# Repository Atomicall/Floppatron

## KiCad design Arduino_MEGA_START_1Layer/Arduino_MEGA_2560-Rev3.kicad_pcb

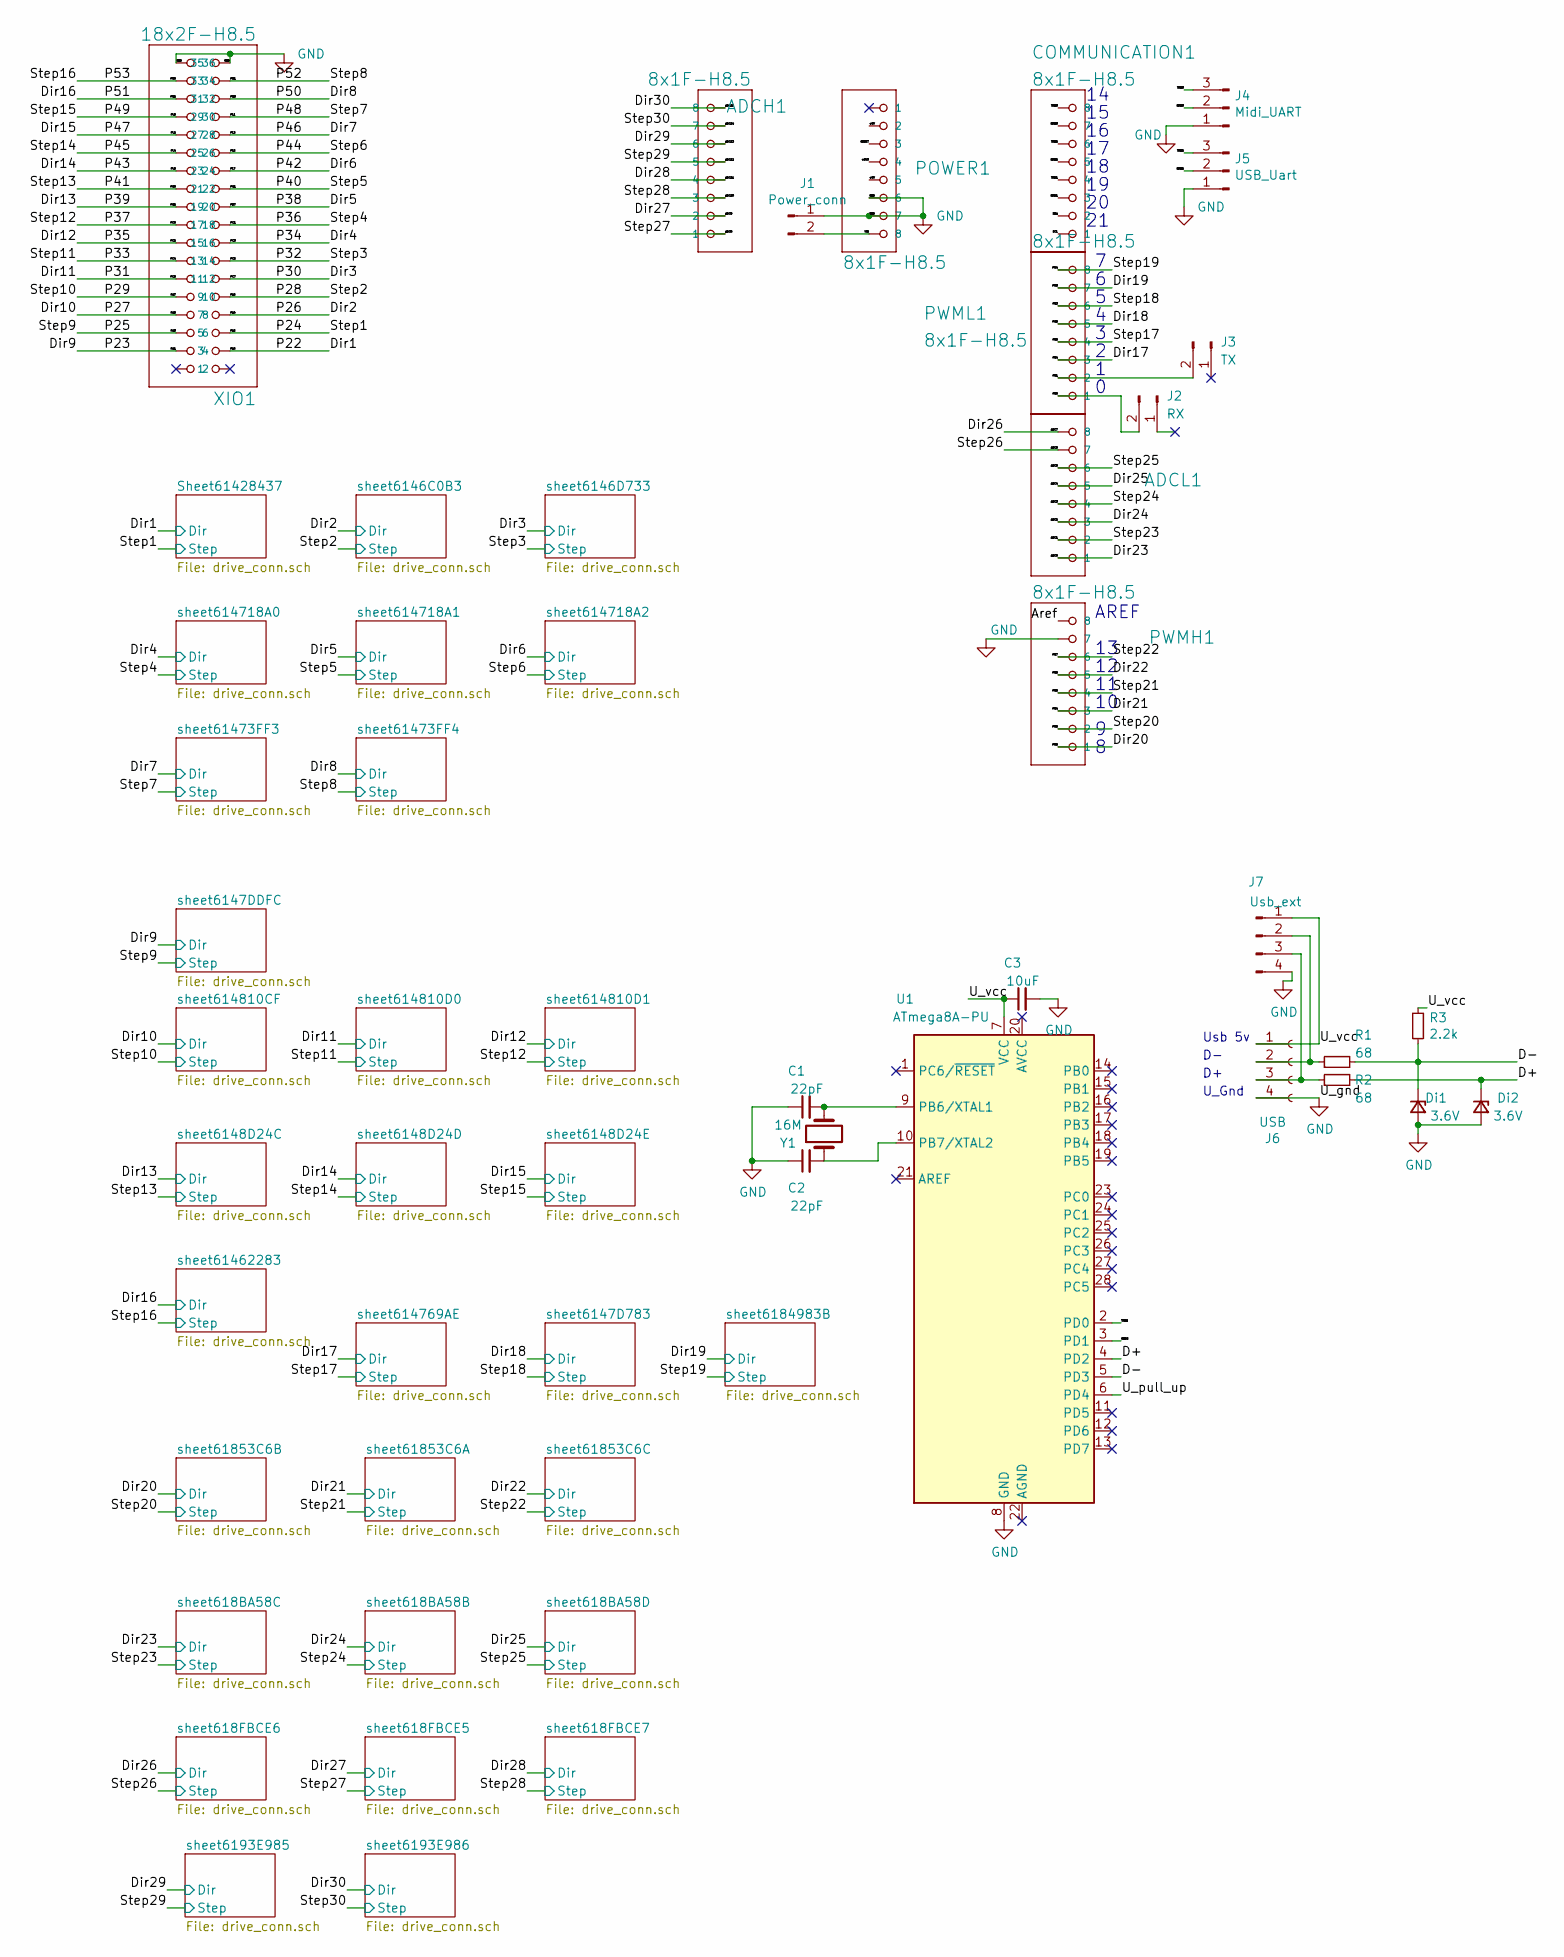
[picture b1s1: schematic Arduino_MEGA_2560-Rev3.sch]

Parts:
ADCH1: 8x1F-H8.5; SMARTPRJ_1X08
ADCL1: 8x1F-H8.5; SMARTPRJ_1X08
C1, C2: 22pF; C_Disc_D3.4mm_W2.1mm_P2.50mm
C3: 10uF; CP_Radial_D5.0mm_P2.00mm
COMMUNICATION1: 8x1F-H8.5; SMARTPRJ_1X08
Di1, Di2: 3.6V; D_DO-41_SOD81_P7.62mm_Horizontal
J1: Power_conn; PinHeader_1x02_P2.54mm_Vertical
J2: RX; PinHeader_1x02_P2.54mm_Vertical
J3: TX; PinHeader_1x02_P2.54mm_Vertical
J4: Midi_UART; PinHeader_1x03_P2.54mm_Vertical
J5: USB_Uart; PinHeader_1x03_P2.54mm_Vertical
J6: USB; usb_type_c_female_board_Aliexpress
J7: Usb_ext; PinSocket_1x04_P2.54mm_Vertical
POWER1: 8x1F-H8.5; SMARTPRJ_1X08
PWMH1: 8x1F-H8.5; PinHeader_1x08_P2.54mm_Vertical
PWML1: 8x1F-H8.5; SMARTPRJ_1X08
R1, R2: 68; R_Axial_DIN0204_L3.6mm_D1.6mm_P2.54mm_Vertical
R3: 2.2k; R_Axial_DIN0204_L3.6mm_D1.6mm_P2.54mm_Vertical
U1: ATmega8A-PU; DIP-28_W7.62mm
XIO1: 18x2F-H8.5; SMARTPRJ_2X18
Y1: 16M; Crystal_HC49-4H_Vertical

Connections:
/+3V3: POWER1.4
/+5V: POWER1.2, POWER1.5
/ADC0: ADCL1.1; also elsewhere on the board
/ADC1: ADCL1.2; also elsewhere on the board
/ADC2: ADCL1.3; also elsewhere on the board
/ADC3: ADCL1.4; also elsewhere on the board
/ADC4: ADCL1.5; also elsewhere on the board
/ADC5: ADCL1.6; also elsewhere on the board
/ADC6: ADCL1.7; also elsewhere on the board
/ADC7: ADCL1.8; also elsewhere on the board
/ADC8: ADCH1.1; also elsewhere on the board
/ADC9: ADCH1.2; also elsewhere on the board
/ADC10: ADCH1.3; also elsewhere on the board
/ADC11: ADCH1.4; also elsewhere on the board
/ADC12: ADCH1.5; also elsewhere on the board
/ADC13: ADCH1.6; also elsewhere on the board
/ADC14: ADCH1.7; also elsewhere on the board
/ADC15: ADCH1.8; also elsewhere on the board
/Aref: PWMH1.8
/D+: Di2.1 (K), R2.2, U1.4 (PD2)
/D-: Di1.1 (K), R1.2, R3.2, U1.5 (PD3)
/Dir1: XIO1.3; also elsewhere on the board
/Dir2: XIO1.7; also elsewhere on the board
/Dir3: XIO1.11; also elsewhere on the board
/Dir4: XIO1.15; also elsewhere on the board
/Dir5: XIO1.19; also elsewhere on the board
/Dir6: XIO1.23; also elsewhere on the board
/Dir7: XIO1.27; also elsewhere on the board
/Dir8: XIO1.31; also elsewhere on the board
/Dir9: XIO1.4; also elsewhere on the board
/Dir10: XIO1.8; also elsewhere on the board
/Dir11: XIO1.12; also elsewhere on the board
/Dir12: XIO1.16; also elsewhere on the board
/Dir13: XIO1.20; also elsewhere on the board
/Dir14: XIO1.24; also elsewhere on the board
/Dir15: XIO1.28; also elsewhere on the board
/Dir16: XIO1.32; also elsewhere on the board
/Dir17: PWML1.3; also elsewhere on the board
/Dir18: PWML1.5; also elsewhere on the board
/Dir19: PWML1.7; also elsewhere on the board
/Dir20: PWMH1.1; also elsewhere on the board
/Dir21: PWMH1.3; also elsewhere on the board
/Dir22: PWMH1.5; also elsewhere on the board
/P24: XIO1.5; also elsewhere on the board
/P25: XIO1.6; also elsewhere on the board
/P28: XIO1.9; also elsewhere on the board
/P29: XIO1.10; also elsewhere on the board
/P32: XIO1.13; also elsewhere on the board
/P33: XIO1.14; also elsewhere on the board
/P36: XIO1.17; also elsewhere on the board
/P37: XIO1.18; also elsewhere on the board
/P40: XIO1.21; also elsewhere on the board
/P41: XIO1.22; also elsewhere on the board
/P44: XIO1.25; also elsewhere on the board
/P45: XIO1.26; also elsewhere on the board
/P48: XIO1.29; also elsewhere on the board
/P49: XIO1.30; also elsewhere on the board
/P52: XIO1.33; also elsewhere on the board
/P53: XIO1.34; also elsewhere on the board
/PB5: PWMH1.4; also elsewhere on the board
/PB7: PWMH1.6; also elsewhere on the board
/PE0: J2.2, PWML1.1
/PE1: J3.2, PWML1.2
/PE3: PWML1.6; also elsewhere on the board
/PE5: PWML1.4; also elsewhere on the board
/PH4: PWML1.8; also elsewhere on the board
/PH6: PWMH1.2; also elsewhere on the board
/RESET: POWER1.3
/RXD1: COMMUNICATION1.3
/RXD2: COMMUNICATION1.5, J5.2, U1.3 (PD1)
/RXD3: COMMUNICATION1.7, J4.2
/SCL: COMMUNICATION1.1
/SDA: COMMUNICATION1.2
/TXD1: COMMUNICATION1.4
/TXD2: COMMUNICATION1.6, J5.3, U1.2 (PD0)
/TXD3: COMMUNICATION1.8, J4.3
/U_pull_up: U1.6 (PD4)
/U_vcc: C3.1, J6.1, J7.1, R3.1, U1.7 (VCC)
/VIN: J1.2, POWER1.8
GND: C1.1, C2.1, C3.2, Di1.2 (A), Di2.2 (A), J1.1, J4.1, J5.1, J6.4, J7.4, POWER1.6, POWER1.7, PWMH1.7, U1.8 (GND), XIO1.35, XIO1.36
unnamed: C1.2, U1.9 (PB6/XTAL1), Y1.2
unnamed: C2.2, U1.10 (PB7/XTAL2), Y1.1
unnamed: J6.2, J7.2, R1.1
unnamed: J6.3, J7.3, R2.1

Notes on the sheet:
AREF
Usb 5v
U_Gnd

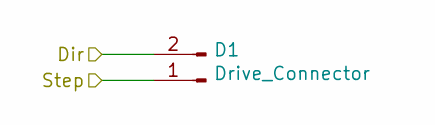
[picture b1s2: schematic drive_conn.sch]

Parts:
D15: Drive_Connector; PinHeader_1x02_P2.54mm_Vertical

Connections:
/Dir1: D15.2; also elsewhere on the board
/P24: D15.1; also elsewhere on the board

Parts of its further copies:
D1, D2, D3, D4, D5, D6, D7, D8, D9, D10, D11, D12, D13, D14, D16, D17, D18, D19, D20, D21, D22, D23, D24, D25, D26, D27, D28, D29, D30: Drive_Connector; PinHeader_1x02_P2.54mm_Vertical

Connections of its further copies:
/ADC0: D24.2; also elsewhere on the board
/ADC1: D24.1; also elsewhere on the board
/ADC2: D23.2; also elsewhere on the board
/ADC3: D23.1; also elsewhere on the board
/ADC4: D25.2; also elsewhere on the board
/ADC5: D25.1; also elsewhere on the board
/ADC6: D27.1; also elsewhere on the board
/ADC7: D27.2; also elsewhere on the board
/ADC8: D26.1; also elsewhere on the board
/ADC9: D26.2; also elsewhere on the board
/ADC10: D28.1; also elsewhere on the board
/ADC11: D28.2; also elsewhere on the board
/ADC12: D29.1; also elsewhere on the board
/ADC13: D29.2; also elsewhere on the board
/ADC14: D30.1; also elsewhere on the board
/ADC15: D30.2; also elsewhere on the board
/Dir2: D1.2; also elsewhere on the board
/Dir3: D2.2; also elsewhere on the board
/Dir4: D3.2; also elsewhere on the board
/Dir5: D4.2; also elsewhere on the board
/Dir6: D5.2; also elsewhere on the board
/Dir7: D6.2; also elsewhere on the board
/Dir8: D7.2; also elsewhere on the board
/Dir9: D8.2; also elsewhere on the board
/Dir10: D9.2; also elsewhere on the board
/Dir11: D10.2; also elsewhere on the board
/Dir12: D11.2; also elsewhere on the board
/Dir13: D12.2; also elsewhere on the board
/Dir14: D13.2; also elsewhere on the board
/Dir15: D14.2; also elsewhere on the board
/Dir16: D16.2; also elsewhere on the board
/Dir17: D18.2; also elsewhere on the board
/Dir18: D17.2; also elsewhere on the board
/Dir19: D19.2; also elsewhere on the board
/Dir20: D21.2; also elsewhere on the board
/Dir21: D20.2; also elsewhere on the board
/Dir22: D22.2; also elsewhere on the board
/P25: D8.1; also elsewhere on the board
/P28: D1.1; also elsewhere on the board
/P29: D9.1; also elsewhere on the board
/P32: D2.1; also elsewhere on the board
/P33: D10.1; also elsewhere on the board
/P36: D3.1; also elsewhere on the board
/P37: D11.1; also elsewhere on the board
/P40: D4.1; also elsewhere on the board
/P41: D12.1; also elsewhere on the board
/P44: D5.1; also elsewhere on the board
/P45: D13.1; also elsewhere on the board
/P48: D6.1; also elsewhere on the board
/P49: D14.1; also elsewhere on the board
/P52: D7.1; also elsewhere on the board
/P53: D16.1; also elsewhere on the board
/PB5: D20.1; also elsewhere on the board
/PB7: D22.1; also elsewhere on the board
/PE3: D17.1; also elsewhere on the board
/PE5: D18.1; also elsewhere on the board
/PH4: D19.1; also elsewhere on the board
/PH6: D21.1; also elsewhere on the board

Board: 2 copper layers, 54 parts (0 on the bottom side), 76 nets, no tracks yet.

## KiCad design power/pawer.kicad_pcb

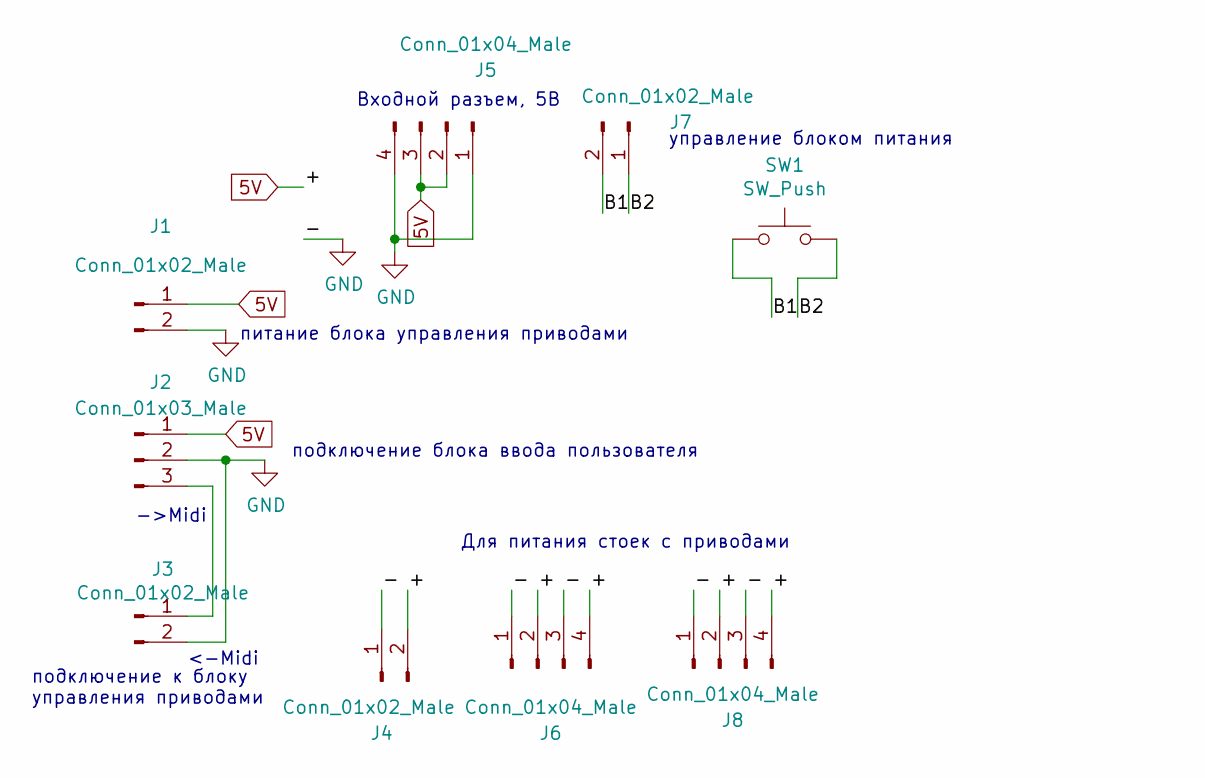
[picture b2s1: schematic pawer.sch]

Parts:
J1, J3, J4, J7: Conn_01x02_Male; PinHeader_1x02_P2.54mm_Horizontal
J2: Conn_01x03_Male; PinHeader_1x03_P2.54mm_Horizontal
J5, J6, J8: Conn_01x04_Male; PinHeader_1x04_P2.54mm_Horizontal
SW1: SW_Push; SW_NKK_GW12LJP

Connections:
5V: J1.1, J2.1, J4.2, J5.2, J5.3, J6.2, J6.4, J8.2, J8.4
/B1: J7.2, SW1.1
/B2: J7.1, SW1.2
GND: J1.2, J2.2, J3.2, J4.1, J5.1, J5.4, J6.1, J6.3, J8.1, J8.3
unnamed: J2.3, J3.1

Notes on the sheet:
Для питания стоек с приводами
<-Midi
->Midi
питание блока управления приводами
управление блоком питания
Входной разъем, 5В
подключение блока ввода пользователя
подключение к блоку управления приводами

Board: 2 copper layers, 9 parts (0 on the bottom side), 5 nets, no tracks yet.
